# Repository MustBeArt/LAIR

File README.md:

# LAIR Pro -- Logic Analyzer Interface for RC-2014 Pro Bus

LAIR is an interface that makes it easy to connect a logic analyzer to the backplane bus of a [RC-2014](https://rc2014.co.uk) Z80-based retro computer. The logic analyzer can capture all activity on the bus and make it available for analysis, without changing the behavior or timing of the RC-2014 system in any way.

The LAIR module plugs into the RC-2014 [Backplane&nbsp;Pro](https://rc2014.co.uk/modules/backplane-pro/), which includes the standard RC-2014 bus and the enhanced RC-2014 bus. It connects all the pins that are present on the Backplane&nbsp;Pro circuit board. All these pins are also brought out to a second set of pins to make it easy to probe the bus.

The LAIR module is compatible with a range of HP (later Agilent, currently Keysight) logic analyzers from 1984 into the 21st century. The LAIR module has four 20-pin headers designed to be compatible with the HP 01650-63203 Termination Adapter, which terminates the probe cables for these models (and others). Each cable supports 16 channels and one clock signal. LAIR assigns signals to the probe pods in such a way that only two pods are required for basic tracing. With four pods connected, every signal on the bus can be captured, with three channels left over and brought out to a separate connector for use in probing non-bus signals. LAIR&nbsp;Pro was developed and tested on an Agilent 1670G.

Besides simply wiring up signals from the bus connector to the probe connectors, LAIR has a bit of circuitry to condition the bus signals. This circuitry is modeled after the circuitry used in the HP Model 64683A Interface Module Z80, and makes it easy for the logic analyzer to accurately trace each bus cycle. With the addition of an available "inverse assembler" file, the logic analyzer can capture and display Z80 instruction cycles in standard mnemonic assembler format.

The circuit board was designed using [KiCad EDA](http://www.kicad.org) and all the design files are included (in the ```hardware``` directory). The ```HP1670G``` directory contains a complete setup for that logic analyzer, including all the RC-2014 bus signals and the HP inverse assembler.

[Schematic of Rev 2 LAIR-Pro module](hardware/LAIR%20Pro%20Rev%202%20module/LAIR-Pro-Rev2-Schematic.pdf) (pdf) NOTE: this schematic has not been reduced to a physical circuit board yet. It has only been tested by making modifications to a Rev 1 circuit board, and not comprehensively tested at that.

## Why a Logic Analyzer?
There are many approaches to debugging programs running on a Z80-based computer such as the RC-2014, but most of them are invasive to some extent. For instance, a debug monitor program can trace execution, but very slowly. Rob Dobson's [BusRaider](https://github.com/robdobsn/PiBusRaider) hardware can theoretically trace every bus access made by the Z80, but still at greatly reduced execution speed. Simulation environments like Alan Cox's [RC2014 Emulator](https://github.com/EtchedPixels/RC2014.git) can trace execution in great detail, not limited by retro hardware speeds, but not on actual hardware. Sometimes there is just no substitute for non-invasive realtime tracing on the actual hardware.

During the CP/M era and beyond, several kinds of solution became available: processor-specific in-circuit emulators, bus analyzers, and general-purpose logic analyzers, each of which had its place. Among them, I'm rather partial to the logic analyzer. It can help solve problems in many kinds of digital systems, not just processor or bus-based systems. I used HP 1630 series logic analyzers to good effect at work in the 1980's and 1990's, and I recently acquired an Agilent (neé HP) 1670G analyzer in pristine condition, thanks to the magic of eBay. These were top of the line professional instruments, designed in the late 1990's. If memory serves, this was the last major revision of HP's original benchtop logic analyzer architecture. This may be stretching the definition of retro a bit out of shape for the CP/M-era purists, but it's old enough for me.

If you were a wealthy company and using a popular processor, you could probably buy a hardware add-on for the logic analyzer that would make it easy to hook up to your target board. In the case of the Z80, that would be HP's _Model 64683A Interface Module Z80_. These interfaces are very hard to find nowadays, so we need to homebrew an alternative.

There were even software packages you could install on the logic analyzer to disassemble the traced opcodes and present the human-readable assembly language integrated with the trace. Miraculously, these *"inverse assembler"* packages are available for download even today, including one for the Z80. What's more, HP's _10391B Inverse Assembler Development Package_ remains available, so you can create your own custom inverse assemblers.

Here's a video on YouTube showing the basic logic analyzer startup procedure:

[https://www.youtube.com/watch?v=011vcvdKTC8](https://www.youtube.com/watch?v=011vcvdKTC8)

HP also made available a Symbol Utility which runs on the logic analyzer and can understand symbols from object files created in several specific object module formats (OMF) that are output by compilers and assemblers. It can also understand a general-purpose ASCII plain text (GPA) format that could be created by hand or by ad hoc tools. The Symbol Utility reads the symbols from these files into a file-based database within the logic analyzer. These symbols are then used in the inverse assembly display and optionally as a column format in the listing view on the logic analyzer's screen.

Even with the inverse assembler and symbol translation, the display on the logic analyzer is fairly primitive. It is also possible to transfer the captured data to a file on an external computer and annotate the traced execution with text from the source code, or from a more sophisticated disassembly listing produced by a reverse engineering tool. The software to do that remains unwritten at this time.

## Logic Analyzer Hookup
The worst part about using a logic analyzer is hooking up all the individual fiddly wires to all the signals. Getting them all right is difficult, and they are fragile and tend to fall off the target board. You can waste a lot of time chasing down problems that turn out to be errors in the logic analyzer hookup. HP's solution to this problem is to replace the individual probe wires at the end of each ribbon cable with a single connector. It turns out that the probe wires also contain electrical termination of each signal, so the single connector device is called a _termination adapter_ by HP or an _isolation adapter_ by Agilent.

As I write in 2019, the termination adapters are readily available on eBay. The HP 01650-63203 Termination Adapter has a standard 20-pin dual-row female pin header connector, carrying one ground connection, sixteen signal connections, two clock signal connections (though the pods have at most one clock input), and a +5V power output that should not be used. The LAIR&nbsp;Pro has four of the mating shrouded sockets.

Simply plug four termination adapters onto the ends of the ribbon cables for pods 1 through 4, and plug the other end of each termination adapter into the corresponding marked port on the LAIR&nbsp;Pro module. Plug the LAIR&nbsp;Pro module into the RC-2014 Pro Backplane (near one end so there's room for the termination adapters). Load the provided logic analyzer setup file to map all the signals to named labels according to LAIR's scheme. If your logic analyzer is not compatible with the provided setup file, refer to the tables below for signal assignments.

In order to use the inverse assembler, the address bus must be labeled ```ADDR``` and the data bus must be labeled ```DATA```. You also need a label ```STAT``` that contains (in most-significant to least-significant order) the signals ```XWR```, ```XIORQ```, ```RFSH```, and ```XM1```. The ```J``` and ```K``` clocks must be connected to ```MREQ``` and ```IORQ```, and the ```L``` clock must be connected to RFSH. If you're able to use the provided setup file, all this is taken care of for you. The ```M``` clock is not used by the inverse assembler or by the standard LAIR&nbsp;Pro setup.

The pin assignments are designed so that you can trace basic bus activity with only pods 1 and 2. However, the inverse assembler depends on the ```L``` clock input which appears on pod&nbsp;3.

The last three signals on pod&nbsp;4 are not needed for bus signals. They are made available on a separate 10-pin connector in case you need to hook them up to other signals on your RC-2014. The other pins on the 10-pin connector are grounds.

The RC-2014 bus is documented along with the [RC-2014 Module Template](http://rc2014.co.uk/1377/module-template/). Pin&nbsp;20 on the secondary bus was originally designated for a secondary clock, but it has come to be used for memory paging between ROM and RAM boards, so we will call it PAGE. Note that the signal names used for the RC-2014 bus do not include any indication of polarity, so we have WR and not WR/ or /WR or !WR or WR-with-a-bar-over-it or anything like that, even though WR is an active low signal.

### Pod 1 Signal Assignments
|Pod Signal|RC-2014 Pin|Signal Name|Description                          |
|----------|-----------|-----------|-------------------------------------|
|     0    |  Main 16  |    A0     | Address bus (least significant bit) |
|     1    |  Main 15  |    A1     | Address bus                         |
|     2    |  Main 14  |    A2     | Address bus                         |
|     3    |  Main 13  |    A3     | Address bus                         |
|     4    |  Main 12  |    A4     | Address bus                         |
|     5    |  Main 11  |    A5     | Address bus                         |
|     6    |  Main 10  |    A6     | Address bus                         |
|     7    |  Main 9   |    A7     | Address bus                         |
|     8    |  Main 8   |    A8     | Address bus                         |
|     9    |  Main 7   |    A9     | Address bus                         |
|    10    |  Main 6   |    A10    | Address bus                         |
|    11    |  Main 5   |    A11    | Address bus                         |
|    12    |  Main 4   |    A12    | Address bus                         |
|    13    |  Main 3   |    A13    | Address bus                         |
|    14    |  Main 2   |    A14    | Address bus                         |
|    15    |  Main 1   |    A15    | Address bus (most significant bit)  |
|  J CLOCK |  Main 23  |   MREQ    | Z80 MREQ, memory request            |

Rising edges on the ```J``` clock input on Pod&nbsp;1 are used to detect memory bus cycles.

### Pod 2 Signal Assignments
|Pod Signal|RC-2014 Pin|Signal Name|Description                          |
|----------|-----------|-----------|-------------------------------------|
|     0    |  Main 27  |    D0     | Data bus (least significant bit)    |
|     1    |  Main 28  |    D1     | Data bus                            |
|     2    |  Main 29  |    D2     | Data bus                            |
|     3    |  Main 30  |    D3     | Data bus                            |
|     4    |  Main 31  |    D4     | Data bus                            |
|     5    |  Main 32  |    D5     | Data bus                            |
|     6    |  Main 33  |    D6     | Data bus                            |
|     7    |  Main 34  |    D7     | Data bus (most significant bit)     |
|     8    |   N/A     |    XWR    | Delayed, inverted version of Z80 WR |
|     9    |   N/A     |   XIORQ   | Delayed version of Z80 IORQ         |
|    10    |   Enh 19  |   RFSH    | Z80 RFSH, refresh request           |
|    11    |   N/A     |    XM1    | Delayed version of Z80 M1           |
|    12    |  Main 25  |    RD     | Z80 RD, read enable                 |
|    13    |  Main 23  |   MREQ    | Z80 MREQ, memory request            |
|    14    |  Main 22  |    INT    | Z80 INT, interrupt request          |
|    15    |  Main 20  |   RESET   | Z80 RESET                           |
|  K CLOCK |  Main 26  |   IORQ    | Z80 IORQ, input/output request      |

Rising edges on the ```K``` clock input on Pod&nbsp;2 are used to detect I/O bus cycles, including interrupt acknowledgement cycles.

### Pod 3 Signal Assignments
|Pod Signal|RC-2014 Pin|Signal Name|Description                          |
|----------|-----------|-----------|-------------------------------------|
|     0    |   Enh 26  |    NMI    | Z80 NMI, non-maskable interrupt     |
|     1    |   Enh 25  |    WAIT   | Z80 WAIT, wait state request        |
|     2    |   Enh 24  |   BUSRQ   | Z80 BUSRQ, bus release request      |
|     3    |   Enh 23  |    HALT   | Z80 HALT, stop processor            |
|     4    |   Enh 22  |  BUSACK   | Z80 BUSACK, bus release acknowledge |
|     5    |   Enh 21  |  CLOCK2   | Secondary clock                     |
|     6    |   Enh 20  |    PAGE   | Paging from ROM to RAM (aka RESET2) |
|     7    |  Main 24  |     WR    | Z80 WR, write enable (not delayed)  |
|     8    |  Main 37  |   USER1   | reserved for user functions         |
|     9    |  Main 38  |   USER2   | reserved for user functions         |
|    10    |  Main 39  |   USER3   | reserved for user functions         |
|    11    |  Main 40  |   USER4   | reserved for user functions         |
|    12    |   Enh 37  |   USER5   | reserved for user functions         |
|    13    |   Enh 38  |   USER6   | reserved for user functions         |
|    14    |   Enh 39  |   USER7   | reserved for user functions         |
|    15    |   Enh 40  |   USER8   | reserved for user functions         |
|  L CLOCK |    N/A    |    RFSH   | Z80 RFSH, refresh request           |

Pod 3's ```L``` clock signal is used as a clock inhibit to prevent DRAM refresh cycles from being logged.

### Pod 4 Signal Assignments
|Pod Signal|RC-2014 Pin|Signal Name|Description                                   |
|----------|-----------|-----------|----------------------------------------------|
|     0    |   Enh 34  |    D8     | 16-bit data bus                              |
|     1    |   Enh 33  |    D9     | 16-bit data bus                              |
|     2    |   Enh 32  |    D10    | 16-bit data bus                              |
|     3    |   Enh 31  |    D11    | 16-bit data bus                              |
|     4    |   Enh 30  |    D12    | 16-bit data bus                              |
|     5    |   Enh 29  |    D13    | 16-bit data bus                              |
|     6    |   Enh 28  |    D14    | 16-bit data bus                              |
|     7    |   Enh 27  |    D15    | 16-bit data bus (most significant bit)       |
|     8    |  Main 36  |    RX     | serial data receive (input to RC-2014)       |
|     9    |  Main 35  |    TX     | serial data transmit (output from RC-2014)   |
|    10    |   Enh 36  |    RX2    | second serial data receive                   |
|    11    |   Enh 35  |    TX2    | second serial data transmit                  |
|    12    |  Main 26  |   IORQ    | Z80 IORQ, input/output request (not delayed) |
|    13    |    N/A    |  Spare 13 | spare logic analyzer channel                 |  
|    14    |    N/A    |  Spare 14 | spare logic analyzer channel                 |  
|    15    |    N/A    |  Spare 15 | spare logic analyzer channel                 |  
|  M CLOCK |  Main 21  |   CLOCK   | Z80 CLOCK, main system clock                 |

Pod 4's ```M``` clock signal is not used by the standard LAIR&nbsp;Pro logic analyzer configuration, but is connected to the main system clock to enable custom configurations.

The three spare inputs appear on their own connector in case you want to use them.

## What About Cheaper Modern Logic Analyzers?

There are now some inexpensive but powerful logic analyzers based on FGPA technology, such as the Logic and Logic&nbsp;Pro line from [Saleae](https://www.saleae.com) (and clones thereof), or any of the commercial and DIY units compatible with the open-source [sigrok](https://sigrok.org) signal analysis software suite. These are extremely useful devices for the retro computer enthusiast, but they are not capable of tracing the RC-2014 bus the same way the LAIR&nbsp;Pro does with an HP/Agilent analyzer. There are two main reasons.

The simple reason is that none of these modern products has enough channels. Saleae tops out at 16 channels, and the widest unit listed on sigrok's Supported Hardware page is 34 channels. A basic trace of bus cycles requires 16 address bits, 8 data bits, and 4 conditioned bus control signals, so a 32-bit analyzer might suffice, but the more common 16-bit models are insufficient. It would take a 64-bit analyzer to capture every signal on the bus, as the LAIR&nbsp;Pro does.

The other reason has to do with what _type_ of logic analyzer we need. All of these modern devices, as far as I know, are what HP calls _timing analyzers_, which means that they sample the data based on a free-running clock generated within the analyzer. The LAIR&nbsp;Pro uses the _state analyzer_ function of the supported logic analyzers. That means it samples the data based on clocks derived from the system under test, the RC-2014 in our case.

With a state analyzer, we can capture exactly one sample for each bus cycle, which is what we need. In order to capture the same information with a timing analyzer, we would need to run the freerunning clock at some multiple of the system clock, which is a bigger multiple of the bus cycle rate. The higher sample rate would generate correspondingly more data, filling up memory faster, and also generates data that isn't nearly as easy to understand. You'd probably want to run a post-processor on the sample data to find the bus cycles and re-create the kind of trace we get directly from a state analyzer.

On the other hand, the modern analyzers have a huge advantage in memory capacity. The vintage HP analyzers store state data to internal memory, where they have room for anywhere from 64K samples to 2M samples (and higher for more recent models). Many of the modern analyzers stream in real time over USB to a modern computer, where storage is practically unlimited by comparison. Even the ones that store to local memory have far more memory than the vintage analyzers do. So, until we hit the streaming bandwidth limit, the extra load of data generated by the timing analyzer is not really a problem.

That leaves the need for a post-processor to help us understand the results in terms of bus cycles. That is a [small matter of programming](https://en.wikipedia.org/wiki/Small_matter_of_programming), but not insurmountable. Perhaps a project for a future day.

One thing the post processor can't help with is triggering. Since the state analyzer is aware of bus cycles in real time, it's easy to set up the analyzer to detect various code execution scenarios in all sorts of flexible ways, and use that to begin, end, and filter our data capturing. The timing analyzers generally have less flexible triggering capabilities. Some smart triggering would still be possible, but it would be messier and probably less flexible on a timing analyzer.

## What About Expensive Modern Logic Analyzers?

I'm sure they're great. Keysight's cheapest current model with enough channels starts at $20,000. And it's not retro, yet.

## Theory of Operation

The Z80 bus has lots of signals for bus management, including some redundancy to make it relatively easy to implement peripheral devices. The most essential of those signals (for a minimal Z80 system) are included in the standard bus on the RC-2014. Other signals for more advanced systems were added with the enhanced bus on the RC-2014&nbsp;Pro.

All bus cycles involve either MREQ (memory request) or IORQ (input/output request). MREQ is active for reads and writes to memory, including opcode fetches and DRAM refreshes. IORQ is active for reads of input ports and writes of output ports, and also for interrupt acknowledgement cycles. As a result, we can capture all these bus cycles by looking for active pulses on MREQ and IORQ.

In order to distinguish the types of bus cycles, we have RD, WR, M1, RFSH.

When found with MREQ, RD is active for memory reads, including opcode fetches and DRAM refreshes. WR is active only for memory writes. M1 is active only for opcode fetches. RFSH is active only for DRAM refreshes. So, we can ignore the RD signal and rely on WR, M1, and RFSH to decode exactly what kind of MREQ cycle we have.

When found with IOREQ, RD is active for input reads and interrupt acknowledges. WR is active only for output writes. M1 is active only for interrupt acknowledges. So we can again ignore RD and rely on WR and M1 to decode the IORQ cycle type.

The obvious implementation of this understanding is to clock the logic state analyzer on the trailing edges of MREQ and IORQ, and decode WR, M1, and RFSH to determine what kind of bus cycle we've captured. That is indeed what we do, but we have to pay attention to the details of Z80 bus timing to make it work. Fortunately, the HP engineers who designed the Model 64683A Interface Module Z80 have shown us the way.

Ideally, we would follow their lead exactly, so as to achieve the same performance guarantees and to maintain complete compatibility with their inverse assembler. The HP designers conservatively chose to buffer every monitored signal. We can't do the same with a standard RC-2014 modules size and through-hole components. We will play a little fast and loose with signal quality concerns and connect directly to the bus signals. This changes the timing of everything by one gate delay.

HP's adapter ran MREQ and IORQ through an inverter and used both of them to clock the state analyzer. We can't do the same, since the other signals aren't delayed. We use MREQ and IORQ directly as ```J``` and ```K``` clock inputs. This doesn't hurt compatibility with the inverse assembler, but it does mean that the logic analyzer's Master Clock has to be configured to detect _rising_ edges on ```J``` or ```K``` instead of falling edges.

The WR signal is not valid at those edges. HP's adapter corrects this problem by running WR through three inverters. We need one fewer gate delay, so we use one inverter and one non-inverting buffer. Likewise, M1 is not quite valid at those edges. HP's adapter, at least according to the description I received, does not address this issue, but we add a non-inverting buffer.

The analyzer is being clocked by both MREQ and IORQ, but it does not automatically keep track of which clock source latched a particular state. In order to find out, we have to delay the clock source (so it remains valid through the transition) and capture it as a state input. HP's adapter runs IORQ through two inverters. We need one fewer gate delay, so we use one non-inverting buffer. We don't need a delayed version of MREQ, because if the state capture wasn't clocked by IORQ, we know it was clocked by MREQ.

For most debug purposes, we don't care to see DRAM refresh cycles. Unless there's a fundamental hardware problem, the DRAM refresh doesn't have anything to do with the flow of program execution. It would be ideal if we could just discard those cycles without storing them. In order to do that on the HP logic analyzer, we need to use a clock qualifying input, and the only signals that can qualify the clocks are other clock inputs. So we connect RFSH to the third clock input ```L```. If we program the analyzer's clock to react to ```J``` (MREQ) or ```K``` only if ```L``` is not active, we don't capture DRAM refresh cycles. If we turn off ```L``` as a clock qualifier, we do capture DRAM refresh cycles, and we can recognize them because we also have RFSH as a captured signal.

That leaves us with a spare clock input ```M```. We don't need it for the inverse assembler. LAIR connects the system clock to ```M``` for possible use in debugging bus cycle timing or operation of peripheral devices that use the system clock. Unfortunately, we don't have a spare clock input for the CLOCK2 secondary clock signal on the enhanced RC-2014 bus.

## Configuring the Logic Analyzer

If possible, use the configuration file (```lair_v1._a```) provided with LAIR&nbsp;Pro. This file is known to work with my Agilent 1670G analyzer. If your analyzer is different, try it anyway and see what happens.

You'll need to transfer two files into your logic analyzer. ```lair_v1._a``` is the configuration file, and ```iz80_i``` is the HP inverse assembler program for Z80. If your logic analyzer has an Ethernet connection to your network, you can transfer these files by FTP. Or, if you have a computer with a 3.5" floppy disk drive, you can copy them onto a floppy and then use the logic analyzer's front panel controls to copy them from the floppy onto the logic analyzer's hard drive.

Then use the logic analyzer's front panel controls to LOAD the configuration from ```lair_v1._a```.

If you can't load the configuration from ```lair_v1._a```, you can enter the configuration manually. Here is a [dump of the logic analyzer configuration](HP1670G/config.txt) and some [screenshots of the logic analyzer configuration](HP1670G/config-screens/) you can refer to. Once you get the analyzer configured correctly, save your configuration to a file so you can use it again next time.

(links in previous paragraph not active yet)

Unfortunately, there's no way to enter the inverse assembler manually. You'll have to get one of the file transfer methods working in order to use it.

After you load the configuration (either ```lair_v1._a``` or one you created), check the listing screen and see if the DATA column has been replaced by an inverse assembler column. If not, you'll need to load the inverse assembler manually. Go back to the Hard Drive screen and LOAD to the ANALYZER from the file ```iz80_i```. Check the listing screen again; it should now be displaying the inverse assembler. If you now save your configuration, the inverse assembler should load automatically next time.

## Use with RC-2014 Pro Backplane

LAIR Pro is designed for use with the Pro Backplane. Plug LAIR&nbsp;Pro into a slot that has the Enhanced Bus connector installed.

The Pro Backplane kit ships with enough 40-pin female headers to populate the Standard Bus on every slot. However, it only ships with a limited number of female headers for the Enhanced Bus, and those connectors are only 20 pins long, which doesn't give access to the four USER pins on the Enhanced Bus connector. You can add Enhanced Bus connectors to the slots that have none, and I suggest you use 24-pin headers. Then you'll need to arrange to have all the modules that use the Enhanced Bus USER pins plugged into these fully populated slots. That includes the LAIR&nbsp;Pro, if you wish to trace the Enhanced Bus USER pins on the logic analyzer.

If you want to go back and add the USER pins to the slots that already have 20-pin connectors on the Enhanced Bus, you'll run into a problem. You can't add female headers next to existing female headers without skipping a pin, because the plastic housings collide. If you're comfortable desoldering, you can remove the existing 20-pin female headers and install new 24-pin ones. That's what I did.

## Use with non-Pro Backplane

If your RC-2014 doesn't support the Enhanced Bus from the RC-2014 Backplane Pro, you can still use LAIR&nbsp;Pro. If you don't need to use the inverse assembler, no special steps are necessary. Of course, you won't see any information on any of the signals from the Enhanced Bus.

In order to run the inverse assembler, you'll need to hook up the RFSH signal. Use the regular individual wires connector on Pod&nbsp;3 (not the termination adapter). Connect the ground wire to a convenient ground on your RC-2014. Connect the ```L``` clock wire to the RFSH signal on your Z80. If your Z80 CPU board has the Enhanced Bus, you can clip onto pin 19 on the Enhanced Bus connector. Otherwise, you can clip directly onto the RFSH/ signal right on the Z80 chip (pin 28 on the usual DIP package).

## Construction

If you've already built your RC-2014, assembling the LAIR-Pro will present few new mysteries.

LAIR Pro has two sets of holes for the RC-2014 Pro bus. Install the usual right-angle dual-row header at the bottom, nearest the edge of the board. The other set of holes is right above that, and is intended to make it easier to connect random probe wires to bus signals. Install straight headers in that set of holes. You can use dual-row male headers or two single-row headers. If you don't think you'll ever want to use these headers for probing, it's perfectly OK to leave them out.

See [Preparing Enhanced Bus Connectors](http://rc2014.co.uk/1426/preparing-enhanced-bus-connectors/) for good advice on installing the right-angle bus connector. Go ahead and remove the first 16 pins as suggested, but don't remove any pins from the other end; LAIR&nbsp;Pro even has room for pin 40.

The [Agilent manual for the Isolation Adapter](HP1670G/manuals/Agilent%20100kOhm%20Isolation%20Adapter.pdf) specifies part numbers from Agilent and from 3M for the mating connector. These part numbers are so obsolete I wasn't even able to find specifications on them. However, the part required is a perfectly ordinary 20-pin dual-row shrouded male header (thank you, HP engineers). I ordered Samtec TST-110-01-G-D ([catalog page](http://suddendocs.samtec.com/catalog_english/tst_th.pdf)) and they work fine. Any other vendor's similar connector would probably work, too. I don't recommend using unshrouded male headers, though they would work. The shrouds help support the weight of the termination adapter and pod cables, and they make it impossible to plug them in backwards or off-by-one.

## Availability

If you want a LAIR Pro right now, you'll have to build it from scratch. You can start with the Rev 2 design files in the hardware directory, output Gerbers, and order from your favorite PCB manufacturer. Then you'll have to find the connectors and other parts. You can do it! If you have never had a board made before, you'll find the experience educational.

If there is interest from the community, I can put together LAIR Pro kits. Please let me know if you are interested in a LAIR Pro kit.

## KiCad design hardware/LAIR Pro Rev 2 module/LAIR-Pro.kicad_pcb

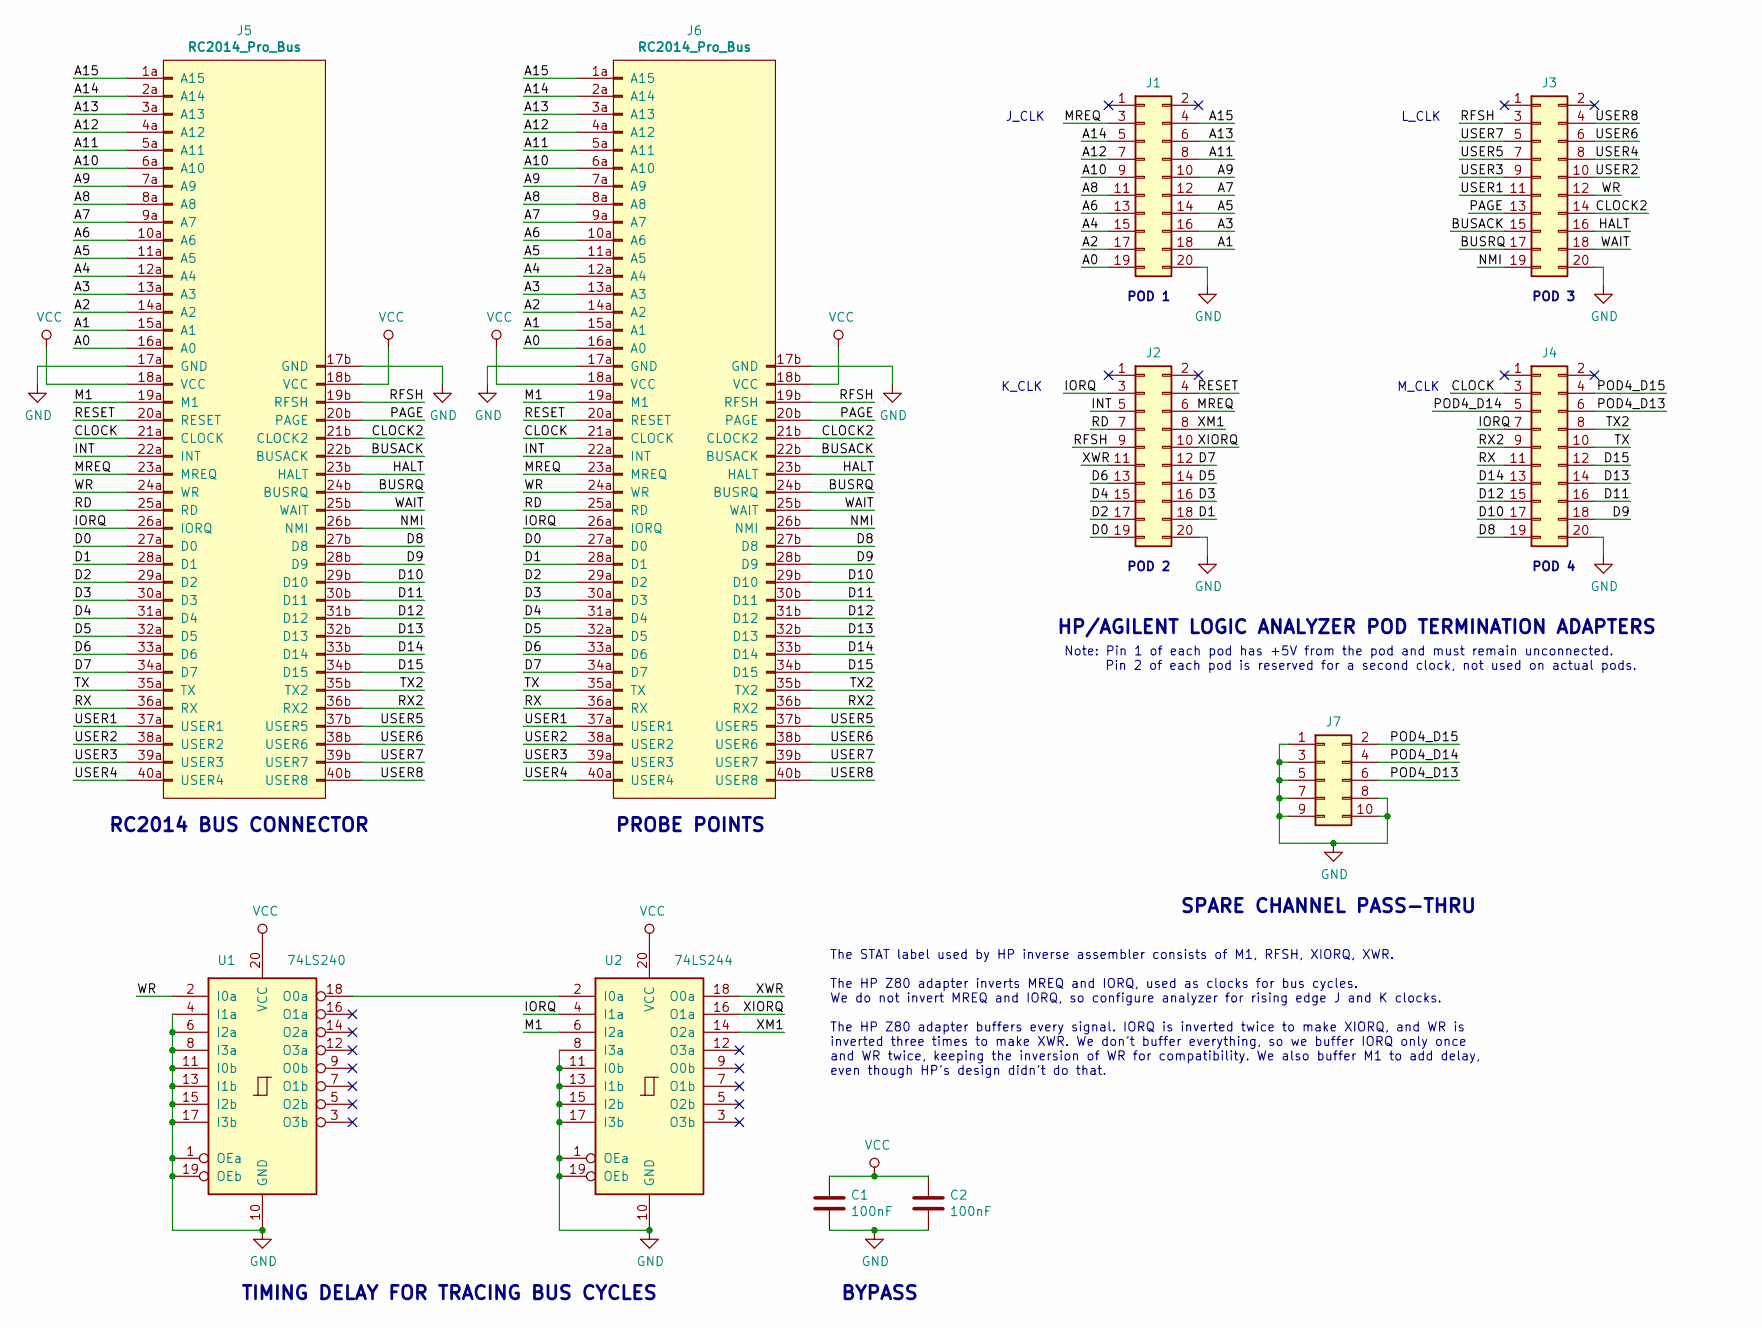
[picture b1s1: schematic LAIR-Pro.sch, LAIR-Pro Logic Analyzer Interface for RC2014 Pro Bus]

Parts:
C1, C2: 100nF; C_Rect_L4.0mm_W2.5mm_P2.50mm
J1, J2, J3, J4: Conn_02x10_Odd_Even; PinHeader_2x10_P2.54mm_Vertical
J5, J6: RC2014_Pro_Bus; PinHeader_RC2014_Pro
J7: Conn_02x05_Odd_Even; PinHeader_2x05_P2.54mm_Vertical
U1: 74LS240; DIP-20_W7.62mm_Socket
U2: 74LS244; DIP-20_W7.62mm_Socket

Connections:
/A0: J1.19, J5.16a (A0), J6.16a (A0)
/A1: J1.18, J5.15a (A1), J6.15a (A1)
/A2: J1.17, J5.14a (A2), J6.14a (A2)
/A3: J1.16, J5.13a (A3), J6.13a (A3)
/A4: J1.15, J5.12a (A4), J6.12a (A4)
/A5: J1.14, J5.11a (A5), J6.11a (A5)
/A6: J1.13, J5.10a (A6), J6.10a (A6)
/A7: J1.12, J5.9a (A7), J6.9a (A7)
/A8: J1.11, J5.8a (A8), J6.8a (A8)
/A9: J1.10, J5.7a (A9), J6.7a (A9)
/A10: J1.9, J5.6a (A10), J6.6a (A10)
/A11: J1.8, J5.5a (A11), J6.5a (A11)
/A12: J1.7, J5.4a (A12), J6.4a (A12)
/A13: J1.6, J5.3a (A13), J6.3a (A13)
/A14: J1.5, J5.2a (A14), J6.2a (A14)
/A15: J1.4, J5.1a (A15), J6.1a (A15)
/BUSACK: J3.15, J5.22b (BUSACK), J6.22b (BUSACK)
/BUSRQ: J3.17, J5.24b (BUSRQ), J6.24b (BUSRQ)
/CLOCK: J4.3, J5.21a (CLOCK), J6.21a (CLOCK)
/CLOCK2: J3.14, J5.21b (CLOCK2), J6.21b (CLOCK2)
/D0: J2.19, J5.27a (D0), J6.27a (D0)
/D1: J2.18, J5.28a (D1), J6.28a (D1)
/D2: J2.17, J5.29a (D2), J6.29a (D2)
/D3: J2.16, J5.30a (D3), J6.30a (D3)
/D4: J2.15, J5.31a (D4), J6.31a (D4)
/D5: J2.14, J5.32a (D5), J6.32a (D5)
/D6: J2.13, J5.33a (D6), J6.33a (D6)
/D7: J2.12, J5.34a (D7), J6.34a (D7)
/D8: J4.19, J5.27b (D8), J6.27b (D8)
/D9: J4.18, J5.28b (D9), J6.28b (D9)
/D10: J4.17, J5.29b (D10), J6.29b (D10)
/D11: J4.16, J5.30b (D11), J6.30b (D11)
/D12: J4.15, J5.31b (D12), J6.31b (D12)
/D13: J4.14, J5.32b (D13), J6.32b (D13)
/D14: J4.13, J5.33b (D14), J6.33b (D14)
/D15: J4.12, J5.34b (D15), J6.34b (D15)
/HALT: J3.16, J5.23b (HALT), J6.23b (HALT)
/INT: J2.5, J5.22a (INT), J6.22a (INT)
/IORQ: J2.3, J4.7, J5.26a (IORQ), J6.26a (IORQ), U2.4 (I1a)
/M1: J5.19a (M1), J6.19a (M1), U2.6 (I2a)
/MREQ: J1.3, J2.6, J5.23a (MREQ), J6.23a (MREQ)
/NMI: J3.19, J5.26b (NMI), J6.26b (NMI)
/PAGE: J3.13, J5.20b (PAGE), J6.20b (PAGE)
/POD4_D13: J4.6, J7.6
/POD4_D14: J4.5, J7.4
/POD4_D15: J4.4, J7.2
/RD: J2.7, J5.25a (RD), J6.25a (RD)
/RESET: J2.4, J5.20a (RESET), J6.20a (RESET)
/RFSH: J2.9, J3.3, J5.19b (RFSH), J6.19b (RFSH)
/RX: J4.11, J5.36a (RX), J6.36a (RX)
/RX2: J4.9, J5.36b (RX2), J6.36b (RX2)
/TX: J4.10, J5.35a (TX), J6.35a (TX)
/TX2: J4.8, J5.35b (TX2), J6.35b (TX2)
/USER1: J3.11, J5.37a (USER1), J6.37a (USER1)
/USER2: J3.10, J5.38a (USER2), J6.38a (USER2)
/USER3: J3.9, J5.39a (USER3), J6.39a (USER3)
/USER4: J3.8, J5.40a (USER4), J6.40a (USER4)
/USER5: J3.7, J5.37b (USER5), J6.37b (USER5)
/USER6: J3.6, J5.38b (USER6), J6.38b (USER6)
/USER7: J3.5, J5.39b (USER7), J6.39b (USER7)
/USER8: J3.4, J5.40b (USER8), J6.40b (USER8)
/WAIT: J3.18, J5.25b (WAIT), J6.25b (WAIT)
/WR: J3.12, J5.24a (WR), J6.24a (WR), U1.2 (I0a)
/XIORQ: J2.10, U2.16 (O1a)
/XM1: J2.8, U2.14 (O2a)
/XWR: J2.11, U2.18 (O0a)
GND: C1.2, C2.2, J1.20, J2.20, J3.20, J4.20, J5.17a (GND), J5.17b (GND), J6.17a (GND), J6.17b (GND), J7.1, J7.3, J7.5, J7.7, J7.8, J7.9, J7.10, U1.1 (OEa), U1.4 (I1a), U1.6 (I2a), U1.8 (I3a), U1.10 (GND), U1.11 (I0b), U1.13 (I1b), U1.15 (I2b), U1.17 (I3b), U1.19 (OEb), U2.1 (OEa), U2.8 (I3a), U2.10 (GND), U2.11 (I0b), U2.13 (I1b), U2.15 (I2b), U2.17 (I3b), U2.19 (OEb)
unnamed: U1.18 (O0a), U2.2 (I0a)
VCC: C1.1, C2.1, J5.18a (VCC), J5.18b (VCC), J6.18a (VCC), J6.18b (VCC), U1.20 (VCC), U2.20 (VCC)

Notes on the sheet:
RC2014 BUS CONNECTOR
PROBE POINTS
POD 1
POD 2
POD 3
POD 4
HP/AGILENT LOGIC ANALYZER POD TERMINATION ADAPTERS
SPARE CHANNEL PASS-THRU
The STAT label used by HP inverse assembler consists of M1, RFSH, XIORQ, XWR. The HP Z80 adapter inverts MREQ and IORQ, used as clocks for bus cycles. We do not invert MREQ and IORQ, so configure analyzer for rising edge J and K clocks. The HP Z80 adapter buffers every signal. IORQ is inverted twic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
Note: Pin 1 of each pod has +5V from the pod and must remain unconnected. Pin 2 of each pod is reserved for a second clock, not used on actual pods.
M_CLK
L_CLK
TIMING DELAY FOR TRACING BUS CYCLES
J_CLK
K_CLK
BYPASS

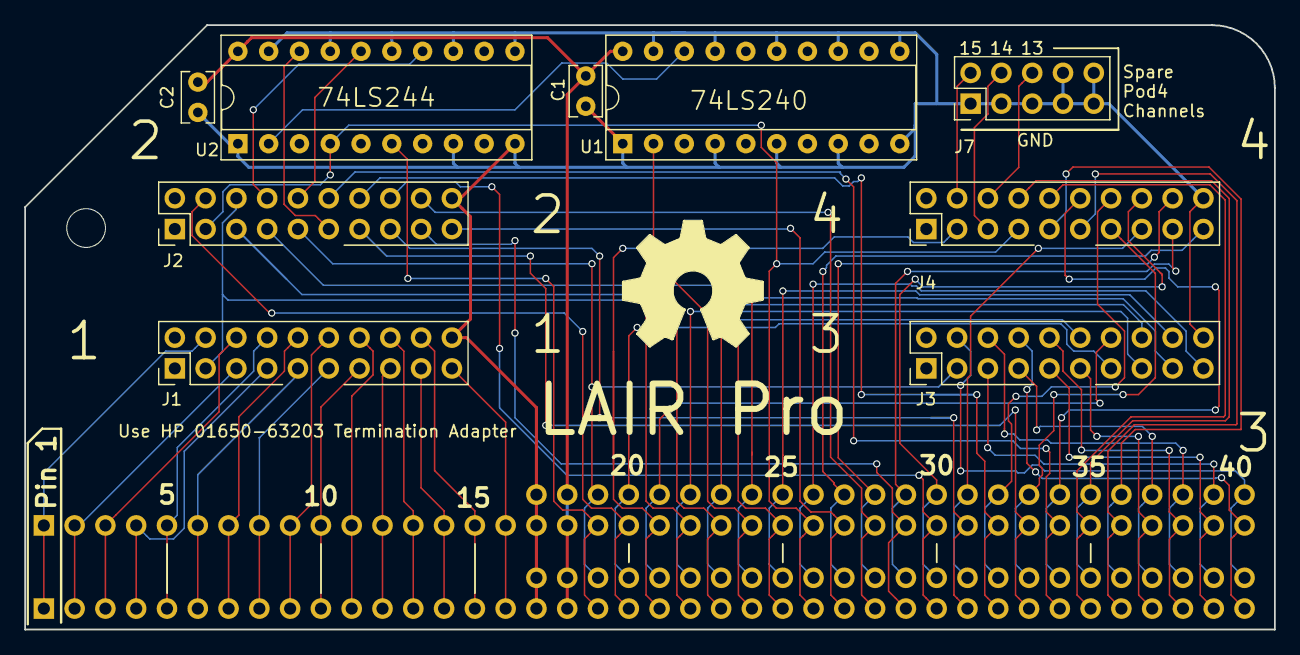
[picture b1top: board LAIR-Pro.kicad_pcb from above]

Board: 2 copper layers, 103.1 x 49.9 mm, 11 parts (0 on the bottom side), 69 nets.

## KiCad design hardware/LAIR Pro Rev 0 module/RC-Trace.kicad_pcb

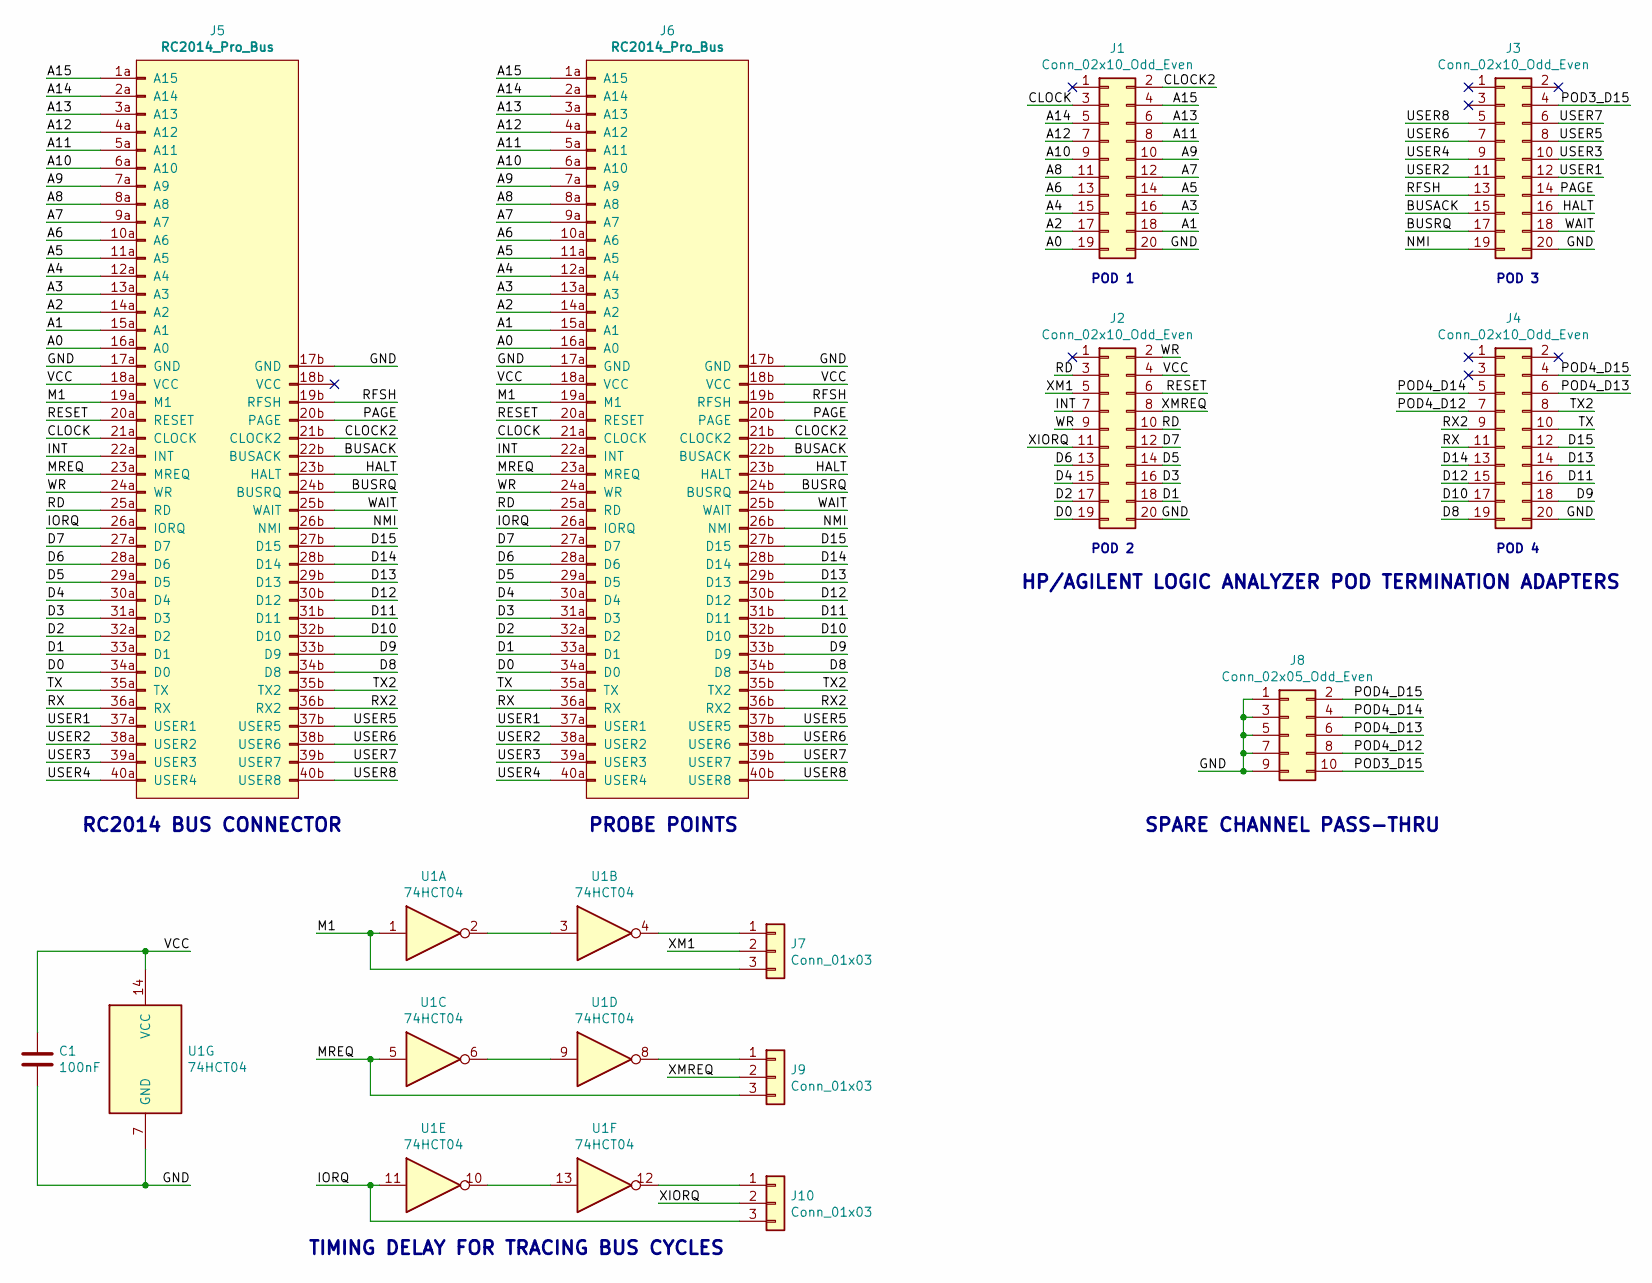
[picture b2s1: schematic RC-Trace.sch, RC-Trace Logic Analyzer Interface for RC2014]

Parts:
C1: 100nF; C_Rect_L4.0mm_W2.5mm_P2.50mm
J1, J2, J3, J4: Conn_02x10_Odd_Even; PinHeader_2x10_P2.54mm_Vertical
J5, J6: RC2014_Pro_Bus; PinHeader_RC2014_Pro
J7, J9, J10: Conn_01x03; PinHeader_1x03_P2.54mm_Vertical
J8: Conn_02x05_Odd_Even; PinHeader_2x05_P2.54mm_Vertical
U1: 74HCT04; DIP-14_W7.62mm_Socket_LongPads

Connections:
/A0: J1.19, J5.16a (A0), J6.16a (A0)
/A1: J1.18, J5.15a (A1), J6.15a (A1)
/A2: J1.17, J5.14a (A2), J6.14a (A2)
/A3: J1.16, J5.13a (A3), J6.13a (A3)
/A4: J1.15, J5.12a (A4), J6.12a (A4)
/A5: J1.14, J5.11a (A5), J6.11a (A5)
/A6: J1.13, J5.10a (A6), J6.10a (A6)
/A7: J1.12, J5.9a (A7), J6.9a (A7)
/A8: J1.11, J5.8a (A8), J6.8a (A8)
/A9: J1.10, J5.7a (A9), J6.7a (A9)
/A10: J1.9, J5.6a (A10), J6.6a (A10)
/A11: J1.8, J5.5a (A11), J6.5a (A11)
/A12: J1.7, J5.4a (A12), J6.4a (A12)
/A13: J1.6, J5.3a (A13), J6.3a (A13)
/A14: J1.5, J5.2a (A14), J6.2a (A14)
/A15: J1.4, J5.1a (A15), J6.1a (A15)
/BUSACK: J3.15, J5.22b (BUSACK), J6.22b (BUSACK)
/BUSRQ: J3.17, J5.24b (BUSRQ), J6.24b (BUSRQ)
/CLOCK: J1.3, J5.21a (CLOCK), J6.21a (CLOCK)
/CLOCK2: J1.2, J5.21b (CLOCK2), J6.21b (CLOCK2)
/D0: J2.19, J5.34a (D0), J6.34a (D0)
/D1: J2.18, J5.33a (D1), J6.33a (D1)
/D2: J2.17, J5.32a (D2), J6.32a (D2)
/D3: J2.16, J5.31a (D3), J6.31a (D3)
/D4: J2.15, J5.30a (D4), J6.30a (D4)
/D5: J2.14, J5.29a (D5), J6.29a (D5)
/D6: J2.13, J5.28a (D6), J6.28a (D6)
/D7: J2.12, J5.27a (D7), J6.27a (D7)
/D8: J4.19, J5.34b (D8), J6.34b (D8)
/D9: J4.18, J5.33b (D9), J6.33b (D9)
/D10: J4.17, J5.32b (D10), J6.32b (D10)
/D11: J4.16, J5.31b (D11), J6.31b (D11)
/D12: J4.15, J5.30b (D12), J6.30b (D12)
/D13: J4.14, J5.29b (D13), J6.29b (D13)
/D14: J4.13, J5.28b (D14), J6.28b (D14)
/D15: J4.12, J5.27b (D15), J6.27b (D15)
/GND: C1.2, J1.20, J2.20, J3.20, J4.20, J5.17a (GND), J5.17b (GND), J6.17a (GND), J6.17b (GND), J8.1, J8.3, J8.5, J8.7, J8.9, U1.7 (GND)
/HALT: J3.16, J5.23b (HALT), J6.23b (HALT)
/INT: J2.7, J5.22a (INT), J6.22a (INT)
/IORQ: J5.26a (IORQ), J6.26a (IORQ), J10.3, U1.11
/M1: J5.19a (M1), J6.19a (M1), J7.3, U1.1
/MREQ: J5.23a (MREQ), J6.23a (MREQ), J9.3, U1.5
/NMI: J3.19, J5.26b (NMI), J6.26b (NMI)
/PAGE: J3.14, J5.20b (PAGE), J6.20b (PAGE)
/POD3_D15: J3.4, J8.10
/POD4_D12: J4.7, J8.8
/POD4_D13: J4.6, J8.6
/POD4_D14: J4.5, J8.4
/POD4_D15: J4.4, J8.2
/RD: J2.3, J2.10, J5.25a (RD), J6.25a (RD)
/RESET: J2.6, J5.20a (RESET), J6.20a (RESET)
/RFSH: J3.13, J5.19b (RFSH), J6.19b (RFSH)
/RX: J4.11, J5.36a (RX), J6.36a (RX)
/RX2: J4.9, J5.36b (RX2), J6.36b (RX2)
/TX: J4.10, J5.35a (TX), J6.35a (TX)
/TX2: J4.8, J5.35b (TX2), J6.35b (TX2)
/USER1: J3.12, J5.37a (USER1), J6.37a (USER1)
/USER2: J3.11, J5.38a (USER2), J6.38a (USER2)
/USER3: J3.10, J5.39a (USER3), J6.39a (USER3)
/USER4: J3.9, J5.40a (USER4), J6.40a (USER4)
/USER5: J3.8, J5.37b (USER5), J6.37b (USER5)
/USER6: J3.7, J5.38b (USER6), J6.38b (USER6)
/USER7: J3.6, J5.39b (USER7), J6.39b (USER7)
/USER8: J3.5, J5.40b (USER8), J6.40b (USER8)
/VCC: C1.1, J2.4, J5.18a (VCC), J6.18a (VCC), J6.18b (VCC), U1.14 (VCC)
/WAIT: J3.18, J5.25b (WAIT), J6.25b (WAIT)
/WR: J2.2, J2.9, J5.24a (WR), J6.24a (WR)
/XIORQ: J2.11, J10.2
/XM1: J2.5, J7.2
/XMREQ: J2.8, J9.2
unnamed: J7.1, U1.4
unnamed: J9.1, U1.8
unnamed: J10.1, U1.12
unnamed: U1.2, U1.3
unnamed: U1.6, U1.9
unnamed: U1.10, U1.13

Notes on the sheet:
RC2014 BUS CONNECTOR
PROBE POINTS
POD 1
POD 2
POD 3
POD 4
HP/AGILENT LOGIC ANALYZER POD TERMINATION ADAPTERS
SPARE CHANNEL PASS-THRU
TIMING DELAY FOR TRACING BUS CYCLES

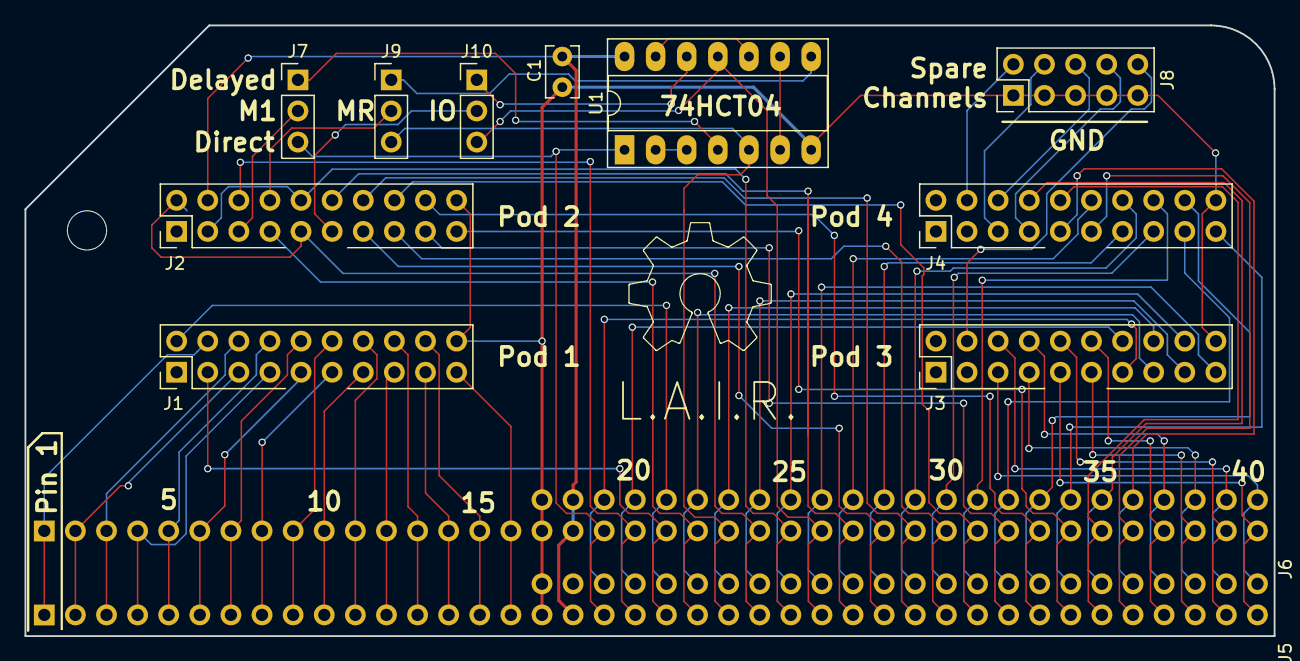
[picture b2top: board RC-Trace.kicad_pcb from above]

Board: 2 copper layers, 102.0 x 49.9 mm, 12 parts (0 on the bottom side), 76 nets.

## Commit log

2019-07-01 Initial commit.
2019-07-03 Use only one clock input per pod
    The documentation for the HP Termination Adapter calls out
    two clock signals on each adapter, but the actual pods on
    the logic analyzers have only one clock per pod, which is
    on pin3 of the Termination Adapter. Pin 2 is unused.
2019-07-03 Put the product name on the back silkscreen
2019-07-04 Adjust timing to account for HP's buffering everything
    On the HP Z80 adapter, they buffer the address bus, the data bus,
    and every other signal through a 74LS241. They then have to add
    more delay to WR and IORQ to make the timing work, and for some
    reason they invert WR while they're at it.
    We don't have room to buffer everything, so we can't follow HP's
    design without expanding the board beyond the RC-2014 form factor.
2019-07-04 Update README with non-buffered bus timing info, etc.
2019-07-09 Match analyzer setup to Rev 1 board
    J and K clocks (MREQ and IORQ) are no longer inverted.
    This diverges from the HP definition but is necessary for
    timing since we aren't buffering every signal.
    STAT symbol was set up for an earlier board design. Corrected
    the patterns to match STAT as defined by HP and implemented
    by Rev 1 module.
2019-07-10 Add Gerbers as submitted for Rev 1 PCB fab
2019-07-10 Add PDF of schematic, linked in README
2019-07-10 Fix schematic URL in README
2019-07-10 Add notes about assembly and backplanes to README
2019-07-10 Add recipes for manipulating logic analyzer screenshots
2019-07-11 Add process history for Rev 1 board
2019-07-20 Rev2: Correct data bus bit order, buffer M1
2019-07-20 Add photos of the Rev 1 module
2019-11-15 Add current status and availability info to README
2019-11-15 Clarify Rev 2 status: PCB designed but not built
2019-11-15 Add photo of the inverse assembler screen
2019-11-17 Add photo of logic analyzer hookup
2019-11-18 Add link to Basic Demonstration video on YouTube
    Also moved the inverse assembly photo up a paragraph, to before
    the discussion about the Symbol Utility, which isn't used in
    the photo.
2019-11-18 Syntax change for embedded video link
2019-11-18 Link to Basic Demo video instead of trying to embed it
    Turns out Github won't really embed a video. We link to it instead,
    grabbing YouTube's thumbnail as a link placeholder.
2019-11-18 Fix the thumbnail embedding syntax
2019-11-18 Just post a link to the Basic Demo video
    Can't seem to get anything fancier to work with Github and YouTube.
2021-11-10 Update README.md
    https://forum.kicad.info/t/warning-avoid-all-links-to-kicad-pcb-org-use-kicad-org/31521
